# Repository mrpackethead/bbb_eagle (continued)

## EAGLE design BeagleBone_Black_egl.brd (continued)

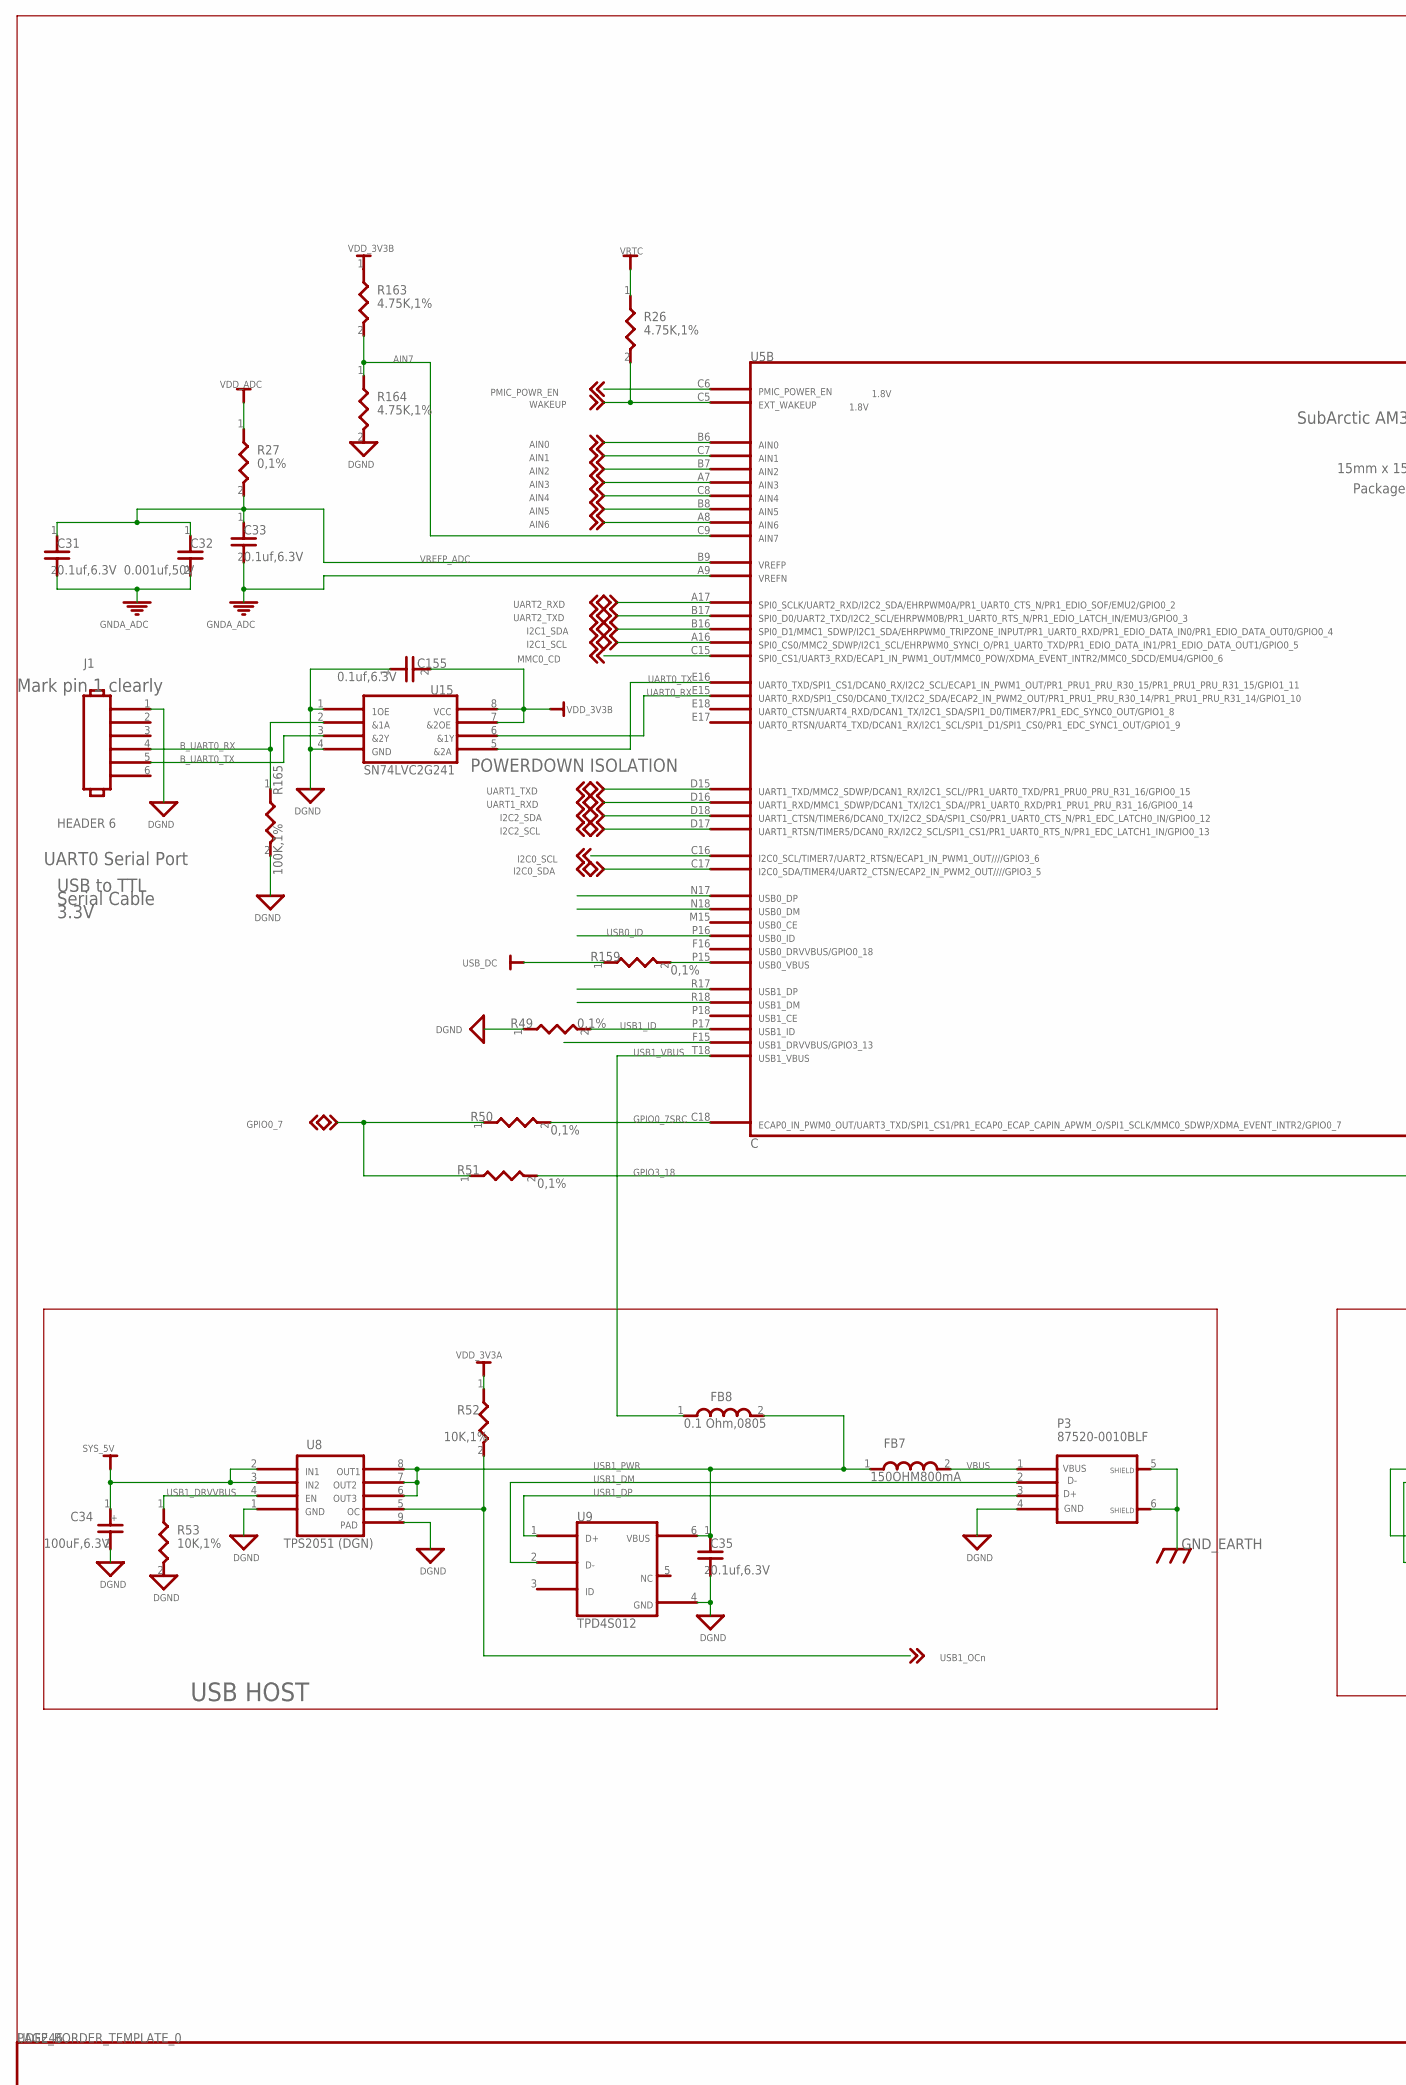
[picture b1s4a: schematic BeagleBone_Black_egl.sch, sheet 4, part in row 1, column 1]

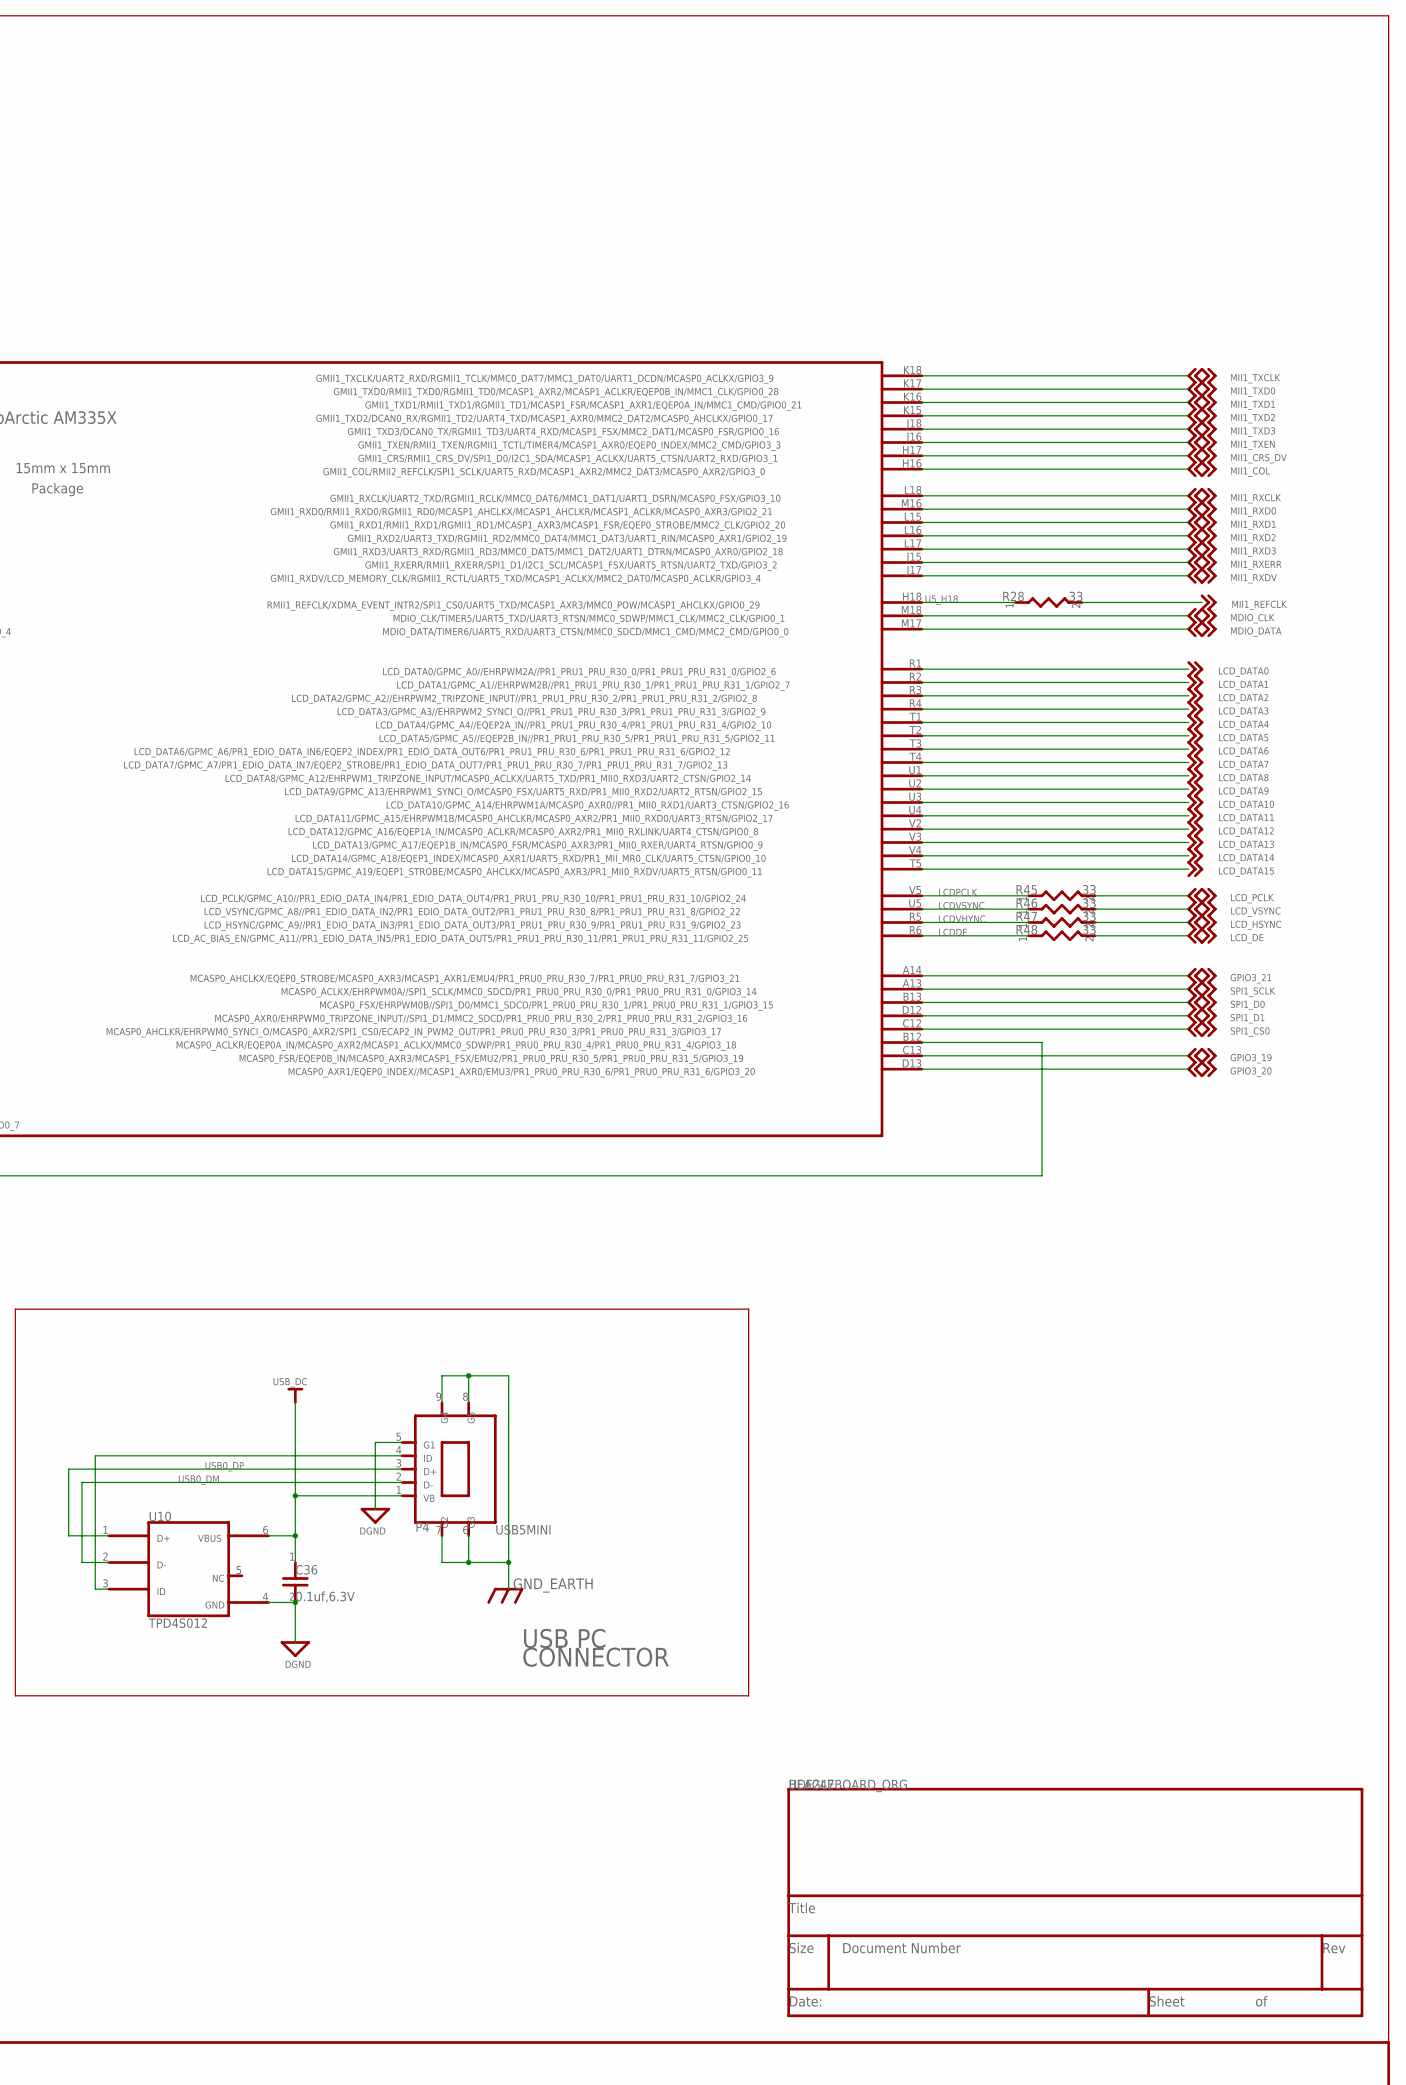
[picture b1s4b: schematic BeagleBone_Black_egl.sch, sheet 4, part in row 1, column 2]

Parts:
C31, C33, C35, C36, C155: 0.1uf,6.3V; 402
C32: 0.001uf,50V; 402
C34: 100uF,6.3V; RD205SMD_250D
FB7: 150OHM800mA; SM-7351-IND-0805
FB8: 0.1 Ohm,0805; SM-7351-IND-0805
J1: HEADER 6; SIP6
P3: 87520-0010BLF; USB_A_SH
P4: USB5MINI; USB5MINI_4SHIELDED_SMD-5
R26, R163, R164: 4.75K,1%; 402
R27, R49, R50, R51, R159: 0,1%; 402
R28, R45, R46, R47, R48: 33; 0402
R52, R53: 10K,1%; 402
R165: 100K,1%; 402
U5: C; AM33XX_15X15
U8: TPS2051 (DGN); DGN-16X60
U9, U10: TPD4S012; U_6_DRY
U15: SN74LVC2G241; U_8_DCU

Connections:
AIN0: U5.B6 (1); also elsewhere on the board
AIN1: U5.C7 (2); also elsewhere on the board
AIN2: U5.B7 (3); also elsewhere on the board
AIN3: U5.A7 (4); also elsewhere on the board
AIN4: U5.C8 (5); also elsewhere on the board
AIN5: U5.B8 (6); also elsewhere on the board
AIN6: U5.A8 (7); also elsewhere on the board
AIN7: R163.2, R164.1, U5.C9 (8)
B_UART0_RX: J1.4, R165.1, U15.2 (1)
B_UART0_TX: J1.5, U15.3 (7)
DGND: C34.2, C35.2, C36.2, C155.1, J1.1, P3.4, P4.5 (7), R49.1, R53.2, R164.2, R165.2, U8.1, U8.9, U9.4, U10.4, U15.1 (3), U15.4 (5); also elsewhere on the board
GNDA_ADC: C31.2, C32.2, C33.2, U5.A9 (10); also elsewhere on the board
GND_EARTH: P3.5, P3.6, P4.6, P4.7 (5), P4.8, P4.9; also elsewhere on the board
GPIO0_7: R50.1, R51.1; also elsewhere on the board
GPIO0_7SRC: R50.2, U5.C18 (86)
GPIO3_18: R51.2, U5.B12 (83)
GPIO3_19: U5.C13 (84); also elsewhere on the board
GPIO3_20: U5.D13 (85); also elsewhere on the board
GPIO3_21: U5.A14 (78); also elsewhere on the board
I2C0_SCL: U5.C16 (49); also elsewhere on the board
I2C0_SDA: U5.C17 (50); also elsewhere on the board
I2C1_SCL: U5.A16 (74); also elsewhere on the board
I2C1_SDA: U5.B16 (73); also elsewhere on the board
I2C2_SCL: U5.D17 (48); also elsewhere on the board
I2C2_SDA: U5.D18 (47); also elsewhere on the board
LCDDE: R48.1, U5.R6 (70)
LCDPCLK: R45.1, U5.V5 (67)
LCDVHYNC: R47.1, U5.R5 (69)
LCDVSYNC: R46.1, U5.U5 (68)
LCD_DATA0: U5.R1 (51); also elsewhere on the board
LCD_DATA1: U5.R2 (52); also elsewhere on the board
LCD_DATA2: U5.R3 (53); also elsewhere on the board
LCD_DATA3: U5.R4 (54); also elsewhere on the board
LCD_DATA4: U5.T1 (55); also elsewhere on the board
LCD_DATA5: U5.T2 (56); also elsewhere on the board
LCD_DATA6: U5.T3 (57); also elsewhere on the board
LCD_DATA7: U5.T4 (58); also elsewhere on the board
LCD_DATA8: U5.U1 (59); also elsewhere on the board
LCD_DATA9: U5.U2 (60); also elsewhere on the board
LCD_DATA10: U5.U3 (61); also elsewhere on the board
LCD_DATA11: U5.U4 (62); also elsewhere on the board
LCD_DATA12: U5.V2 (63); also elsewhere on the board
LCD_DATA13: U5.V3 (64); also elsewhere on the board
LCD_DATA14: U5.V4 (65); also elsewhere on the board
LCD_DATA15: U5.T5 (66); also elsewhere on the board
LCD_DE: R48.2; also elsewhere on the board
LCD_HSYNC: R47.2; also elsewhere on the board
LCD_PCLK: R45.2; also elsewhere on the board
LCD_VSYNC: R46.2; also elsewhere on the board
MDIO_CLK: U5.M18 (43); also elsewhere on the board
MDIO_DATA: U5.M17 (44); also elsewhere on the board
MII1_COL: U5.H16 (27); also elsewhere on the board
MII1_CRS_DV: U5.H17 (28); also elsewhere on the board
MII1_REFCLK: R28.2; also elsewhere on the board
MII1_RXCLK: U5.L18 (37); also elsewhere on the board
MII1_RXD0: U5.M16 (38); also elsewhere on the board
MII1_RXD1: U5.L15 (39); also elsewhere on the board
MII1_RXD2: U5.L16 (40); also elsewhere on the board
MII1_RXD3: U5.L17 (41); also elsewhere on the board
MII1_RXDV: U5.J17 (36); also elsewhere on the board
MII1_RXERR: U5.J15 (35); also elsewhere on the board
MII1_TXCLK: U5.K18 (33); also elsewhere on the board
MII1_TXD0: U5.K17 (29); also elsewhere on the board
MII1_TXD1: U5.K16 (30); also elsewhere on the board
MII1_TXD2: U5.K15 (31); also elsewhere on the board
MII1_TXD3: U5.J18 (32); also elsewhere on the board
MII1_TXEN: U5.J16 (34); also elsewhere on the board
MMC0_CD: U5.C15 (75); also elsewhere on the board
N22155575: R159.2, U5.P15 (18)
PMIC_POWR_EN: U5.C6 (76); also elsewhere on the board
SPI1_CS0: U5.C12 (82); also elsewhere on the board
SPI1_D0: U5.B13 (80); also elsewhere on the board
SPI1_D1: U5.D12 (81); also elsewhere on the board
SPI1_SCLK: U5.A13 (79); also elsewhere on the board
SYS_5V: C34.1, U8.2, U8.3; also elsewhere on the board
U5_H18: R28.1, U5.H18 (42)
UART0_RX: U5.E15 (12), U15.6 (8)
UART0_TX: U5.E16 (11), U15.5 (6)
UART1_RXD: U5.D16 (46); also elsewhere on the board
UART1_TXD: U5.D15 (45); also elsewhere on the board
UART2_RXD: U5.A17 (71); also elsewhere on the board
UART2_TXD: U5.B17 (72); also elsewhere on the board
USB0_DM: P4.2 (1), U5.N18 (16), U10.2
USB0_DP: P4.3 (2), U5.N17 (15), U10.1
USB0_ID: P4.4, U5.P16 (23), U10.3 (6)
USB1_DM: P3.2 (3), U5.R18 (21), U9.2
USB1_DP: P3.3 (2), U5.R17 (20), U9.1
USB1_DRVVBUS: R53.1, U5.F15 (26), U8.4
USB1_ID: R49.2, U5.P17 (22)
USB1_OCN: R52.2, U8.5 (8); also elsewhere on the board
USB1_PWR: C35.1, FB7.1, FB8.2, U8.6 (5), U8.7 (6), U8.8 (7), U9.6 (3)
USB1_VBUS: FB8.1, U5.T18 (25)
USB_DC: C36.1, P4.1 (3), R159.1, U10.6 (3); also elsewhere on the board
VBUS: FB7.2, P3.1
VDD_3V3A: R52.1; also elsewhere on the board
VDD_3V3B: C155.2, R163.1, U15.7 (2), U15.8 (4); also elsewhere on the board
VDD_ADC: R27.1; also elsewhere on the board
VREFP_ADC: C31.1, C32.1, C33.1, R27.2, U5.B9 (9)
VRTC: R26.1; also elsewhere on the board
WAKEUP: R26.2, U5.C5 (77); also elsewhere on the board

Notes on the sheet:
USB HOST
USB PC
CONNECTOR
UART0 Serial Port
USB to TTL
Serial Cable
3.3V
Mark pin 1 clearly
POWERDOWN ISOLATION
DGND
GND_EARTH
I2C0_SCL
I2C0_SDA
PMIC_POWR_EN
SYS_5V
USB_DC
VDD_3V3A
VDD_3V3B
VRTC
WAKEUP
GPIO3_20
GPIO3_21
MMC0_CD
USB1_OCn
AIN0
AIN1
AIN2
AIN3
AIN4
AIN5
AIN6
AIN7
B_UART0_RX
B_UART0_TX
GNDA_ADC
GPIO0_7
GPIO0_7SRC
GPIO3_18
GPIO3_19
I2C1_SCL

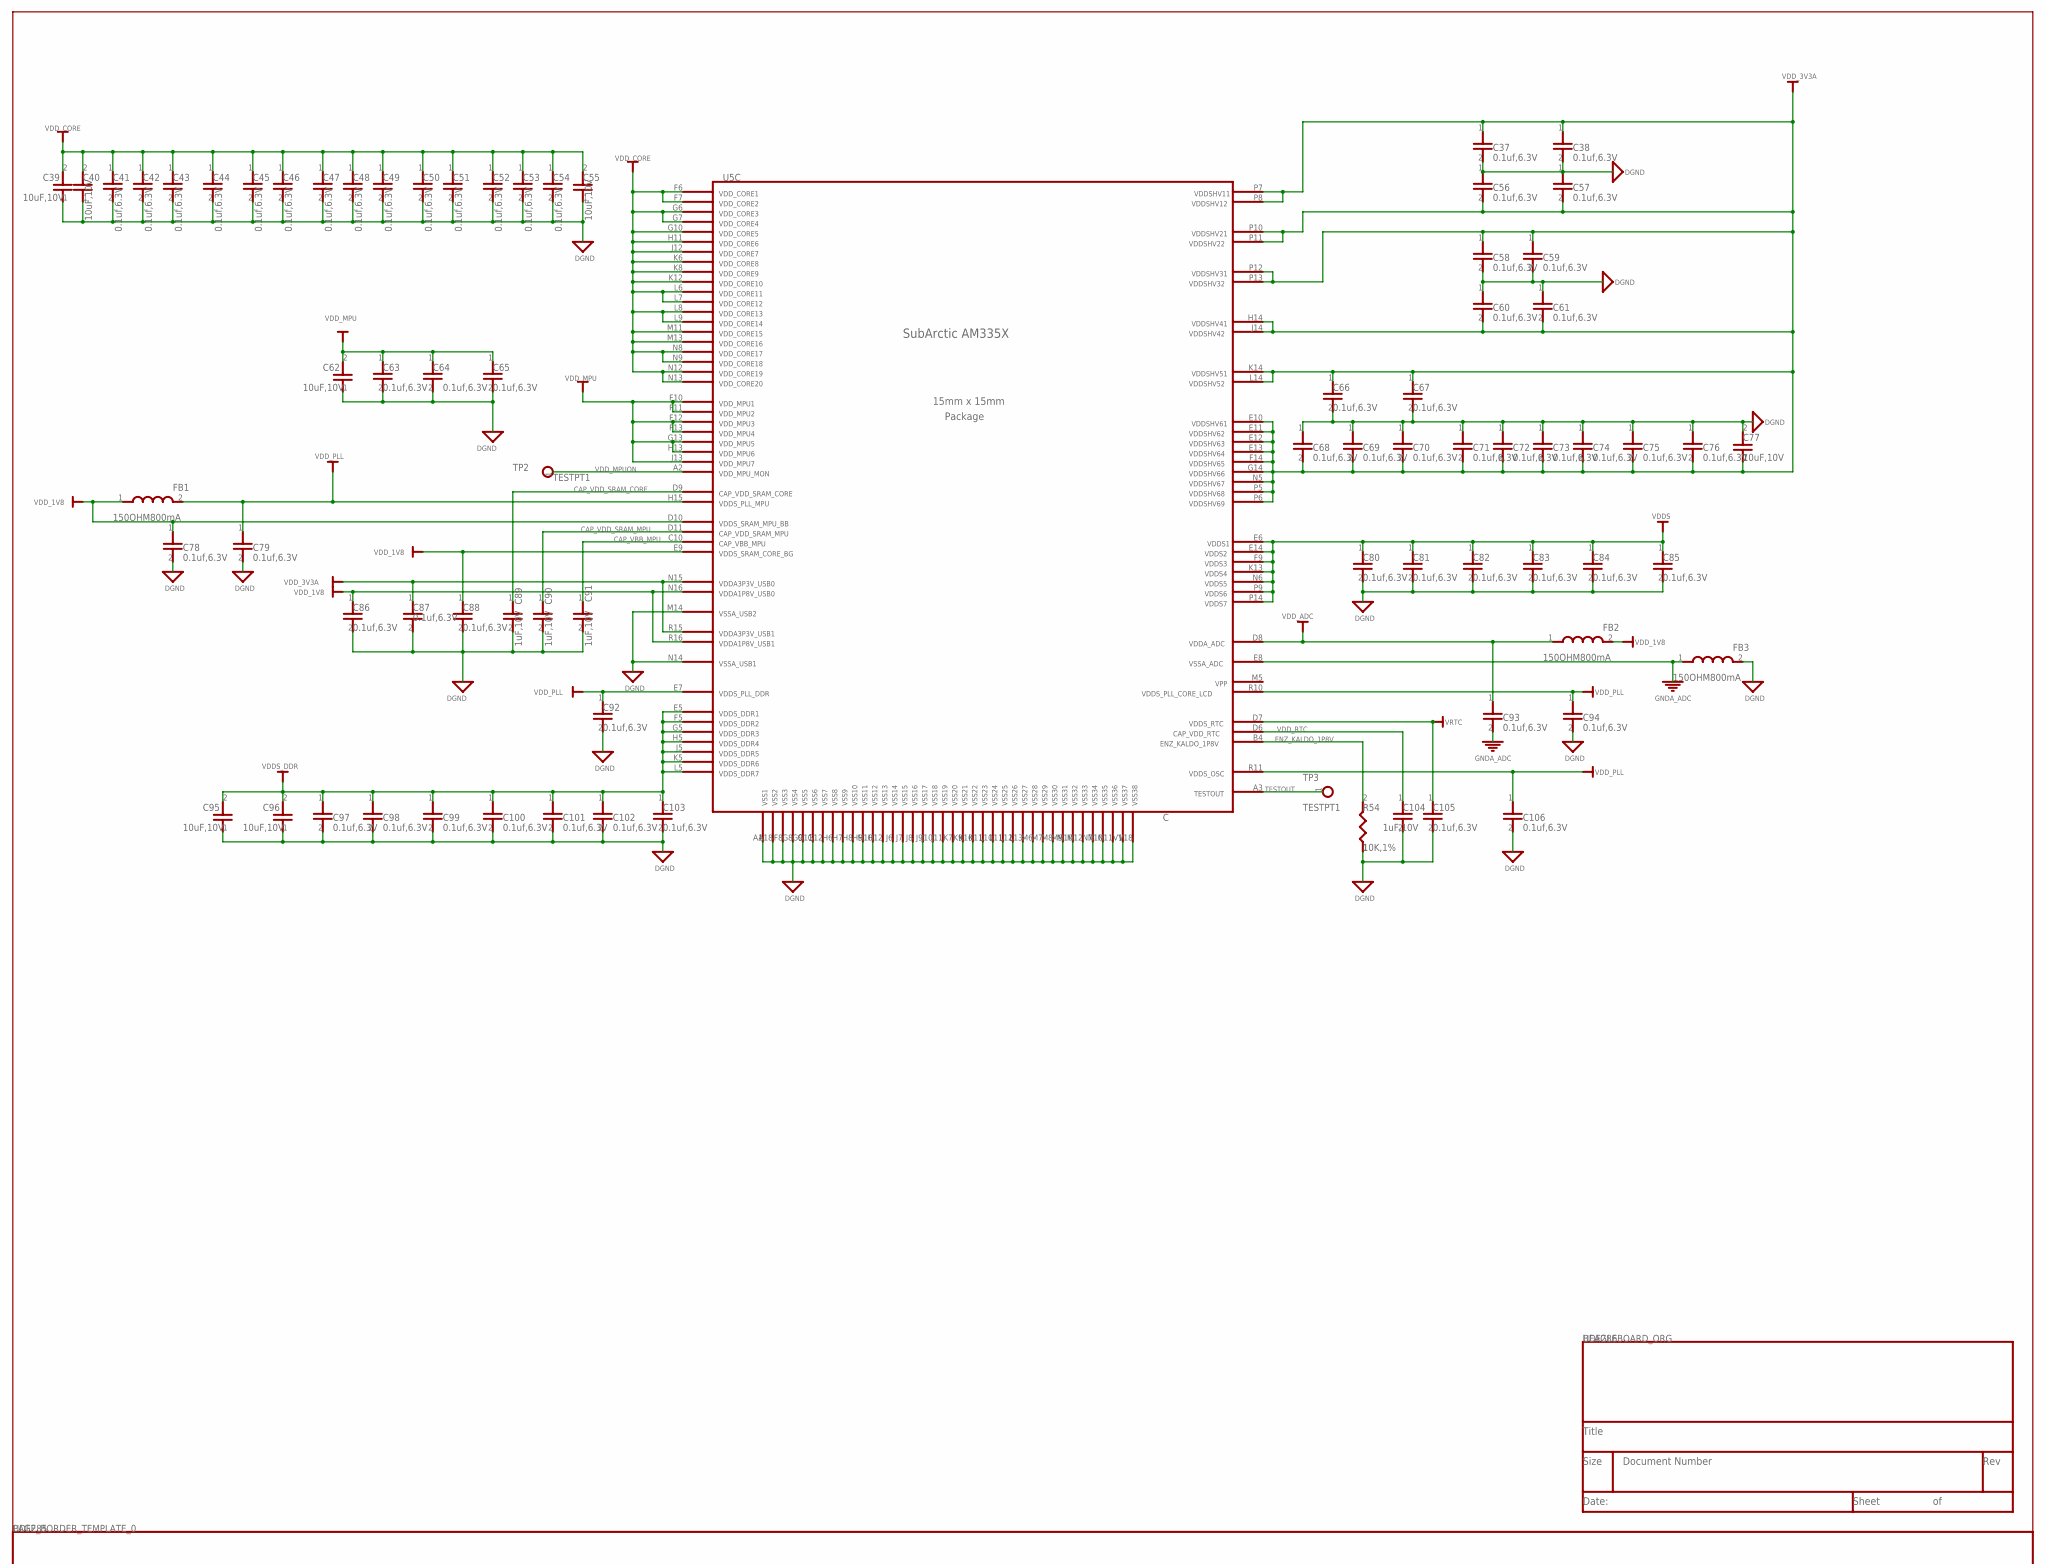
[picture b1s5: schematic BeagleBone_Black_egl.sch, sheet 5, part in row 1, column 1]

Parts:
C37, C38, C41, C42, C43, C44, C45, C46, C47, C48, C49, C50, C51, C52, C53, C54, C56, C57, C58, C59, C60, C61, C63, C64, C65, C66, C67, C68, C69, C70, C71, C72, C73, C74, C75, C76, C78, C79, C80, C81, C82, C83, C84, C85, C86, C87, C88, C92, C93, C94, C97, C98, C99, C100, C101, C102, C103, C105, C106: 0.1uf,6.3V; 402
C39, C40, C55, C62, C77, C95, C96: 10uF,10V; 805
C89, C90, C91, C104: 1uF,10V; 402
FB1, FB2, FB3: 150OHM800mA; SM-7351-IND-0805
R54: 10K,1%; 402
TP2, TP3: TESTPT1; TP60C_SMD
U5: C; AM33XX_15X15

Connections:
CAP_VBB_MPU: C91.1, U5.C10 (76)
CAP_VDD_SRAM_CORE: C89.1, U5.D9 (68)
CAP_VDD_SRAM_MPU: C90.1, U5.D11 (77)
DGND: C37.2, C38.2, C39.1, C40.1, C41.2, C42.2, C43.2, C44.2, C45.2, C46.2, C47.2, C48.2, C49.2, C50.2, C51.2, C52.2, C53.2, C54.2, C55.1, C56.1, C57.1, C58.2, C59.2, C60.1, C61.1, C62.1, C63.2, C64.2, C65.2, C66.2, C67.2, C68.1, C69.1, C70.1, C71.1, C72.1, C73.1, C74.1, C75.1, C76.1, C77.2, C78.2, C79.2, C80.2, C81.2, C82.2, C83.2, C84.2, C85.2, C86.2, C87.2, C88.2, C89.2, C90.2, C91.2, C92.2, C94.2, C95.1, C96.1, C97.2, C98.2, C99.2, C100.2, C101.2, C102.2, C103.2, C104.2, C105.2, C106.2, FB3.2, R54.1, U5.A1 (1), U5.A18 (2), U5.F8 (4), U5.G8 (6), U5.G9 (5), U5.G11 (14), U5.G12 (101), U5.H6 (7), U5.H7 (16), U5.H8 (18), U5.H9 (8), U5.H10 (9), U5.H12 (15), U5.J6 (24), U5.J7 (10), U5.J8 (11), U5.J9 (12), U5.J10 (13), U5.J11 (27), U5.K7 (17), U5.K9 (19), U5.K10 (20), U5.K11 (21), U5.L10 (35), U5.L11 (23), U5.L12 (29), U5.L13 (36), U5.M6 (25), U5.M7 (26), U5.M8 (3), U5.M9 (28), U5.M10 (30), U5.M12 (22), U5.M14 (85), U5.N7 (31), U5.N10 (33), U5.N11 (34), U5.N14 (82), U5.V1 (37), U5.V18 (32); also elsewhere on the board
ENZ_KALDO_1P8V: R54.2, U5.B4 (99)
GNDA_ADC: C93.2, FB3.1, U5.E8 (87); also elsewhere on the board
TESTOUT: TP3.1, U5.A3 (100)
VDDS: C80.1, C81.1, C82.1, C83.1, C84.1, C85.1, U5.E6 (62), U5.E14 (63), U5.F9 (64), U5.K13 (65), U5.N6 (66), U5.P9 (67), U5.P14 (120); also elsewhere on the board
VDDS_DDR: C95.2, C96.2, C97.1, C98.1, C99.1, C100.1, C101.1, C102.1, C103.1, U5.E5 (90), U5.F5 (91), U5.G5 (92), U5.H5 (93), U5.J5 (89), U5.K5 (94), U5.L5 (95); also elsewhere on the board
VDD_1V8: C78.1, C86.1, C88.1, FB1.1, FB2.2, U5.D10 (75), U5.E9 (69), U5.N16 (84), U5.R16 (81); also elsewhere on the board
VDD_3V3A: C37.1, C38.1, C56.2, C57.2, C58.1, C59.1, C60.2, C61.2, C66.1, C67.1, C68.2, C69.2, C70.2, C71.2, C72.2, C73.2, C74.2, C75.2, C76.2, C77.1, C87.1, U5.E10 (111), U5.E11 (112), U5.E12 (113), U5.E13 (114), U5.F14 (115), U5.G14 (116), U5.H14 (59), U5.J14 (58), U5.K14 (60), U5.L14 (61), U5.N5 (117), U5.N15 (83), U5.P5 (118), U5.P6 (119), U5.P7 (53), U5.P8 (54), U5.P10 (55), U5.P11 (96), U5.P12 (56), U5.P13 (57), U5.R15 (80); also elsewhere on the board
VDD_ADC: C93.1, FB2.1, U5.D8 (72); also elsewhere on the board
VDD_CORE: C39.2, C40.2, C41.1, C42.1, C43.1, C44.1, C45.1, C46.1, C47.1, C48.1, C49.1, C50.1, C51.1, C52.1, C53.1, C54.1, C55.2, U5.F6 (38), U5.F7 (39), U5.G6 (40), U5.G7 (42), U5.G10 (43), U5.H11 (45), U5.J12 (46), U5.K6 (47), U5.K8 (97), U5.K12 (49), U5.L6 (50), U5.L7 (51), U5.L8 (52), U5.L9 (98), U5.M11 (102), U5.M13 (103), U5.N8 (104), U5.N9 (105), U5.N12 (106), U5.N13 (107); also elsewhere on the board
VDD_MPU: C62.2, C63.1, C64.1, C65.1, U5.F10 (41), U5.F11 (44), U5.F12 (48), U5.F13 (88), U5.G13 (108), U5.H13 (109), U5.J13 (110); also elsewhere on the board
VDD_MPUON: TP2.1, U5.A2 (121)
VDD_PLL: C79.1, C92.1, C94.1, C106.1, FB1.2, U5.E7 (86), U5.H15 (79), U5.R10 (71), U5.R11 (70)
VDD_RTC: C104.1, U5.D6 (73)
VRTC: C105.1, U5.D7 (74); also elsewhere on the board

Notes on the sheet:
DGND
VDDS
VDDS_DDR
VDD_1V8
VDD_3V3A
VDD_CORE
VDD_MPU
VRTC
GNDA_ADC
VDD_ADC
CAP_VBB_MPU
CAP_VDD_SRAM_CORE
CAP_VDD_SRAM_MPU
ENZ_KALDO_1P8V
TESTOUT
VDD_MPUON
VDD_PLL
VDD_RTC

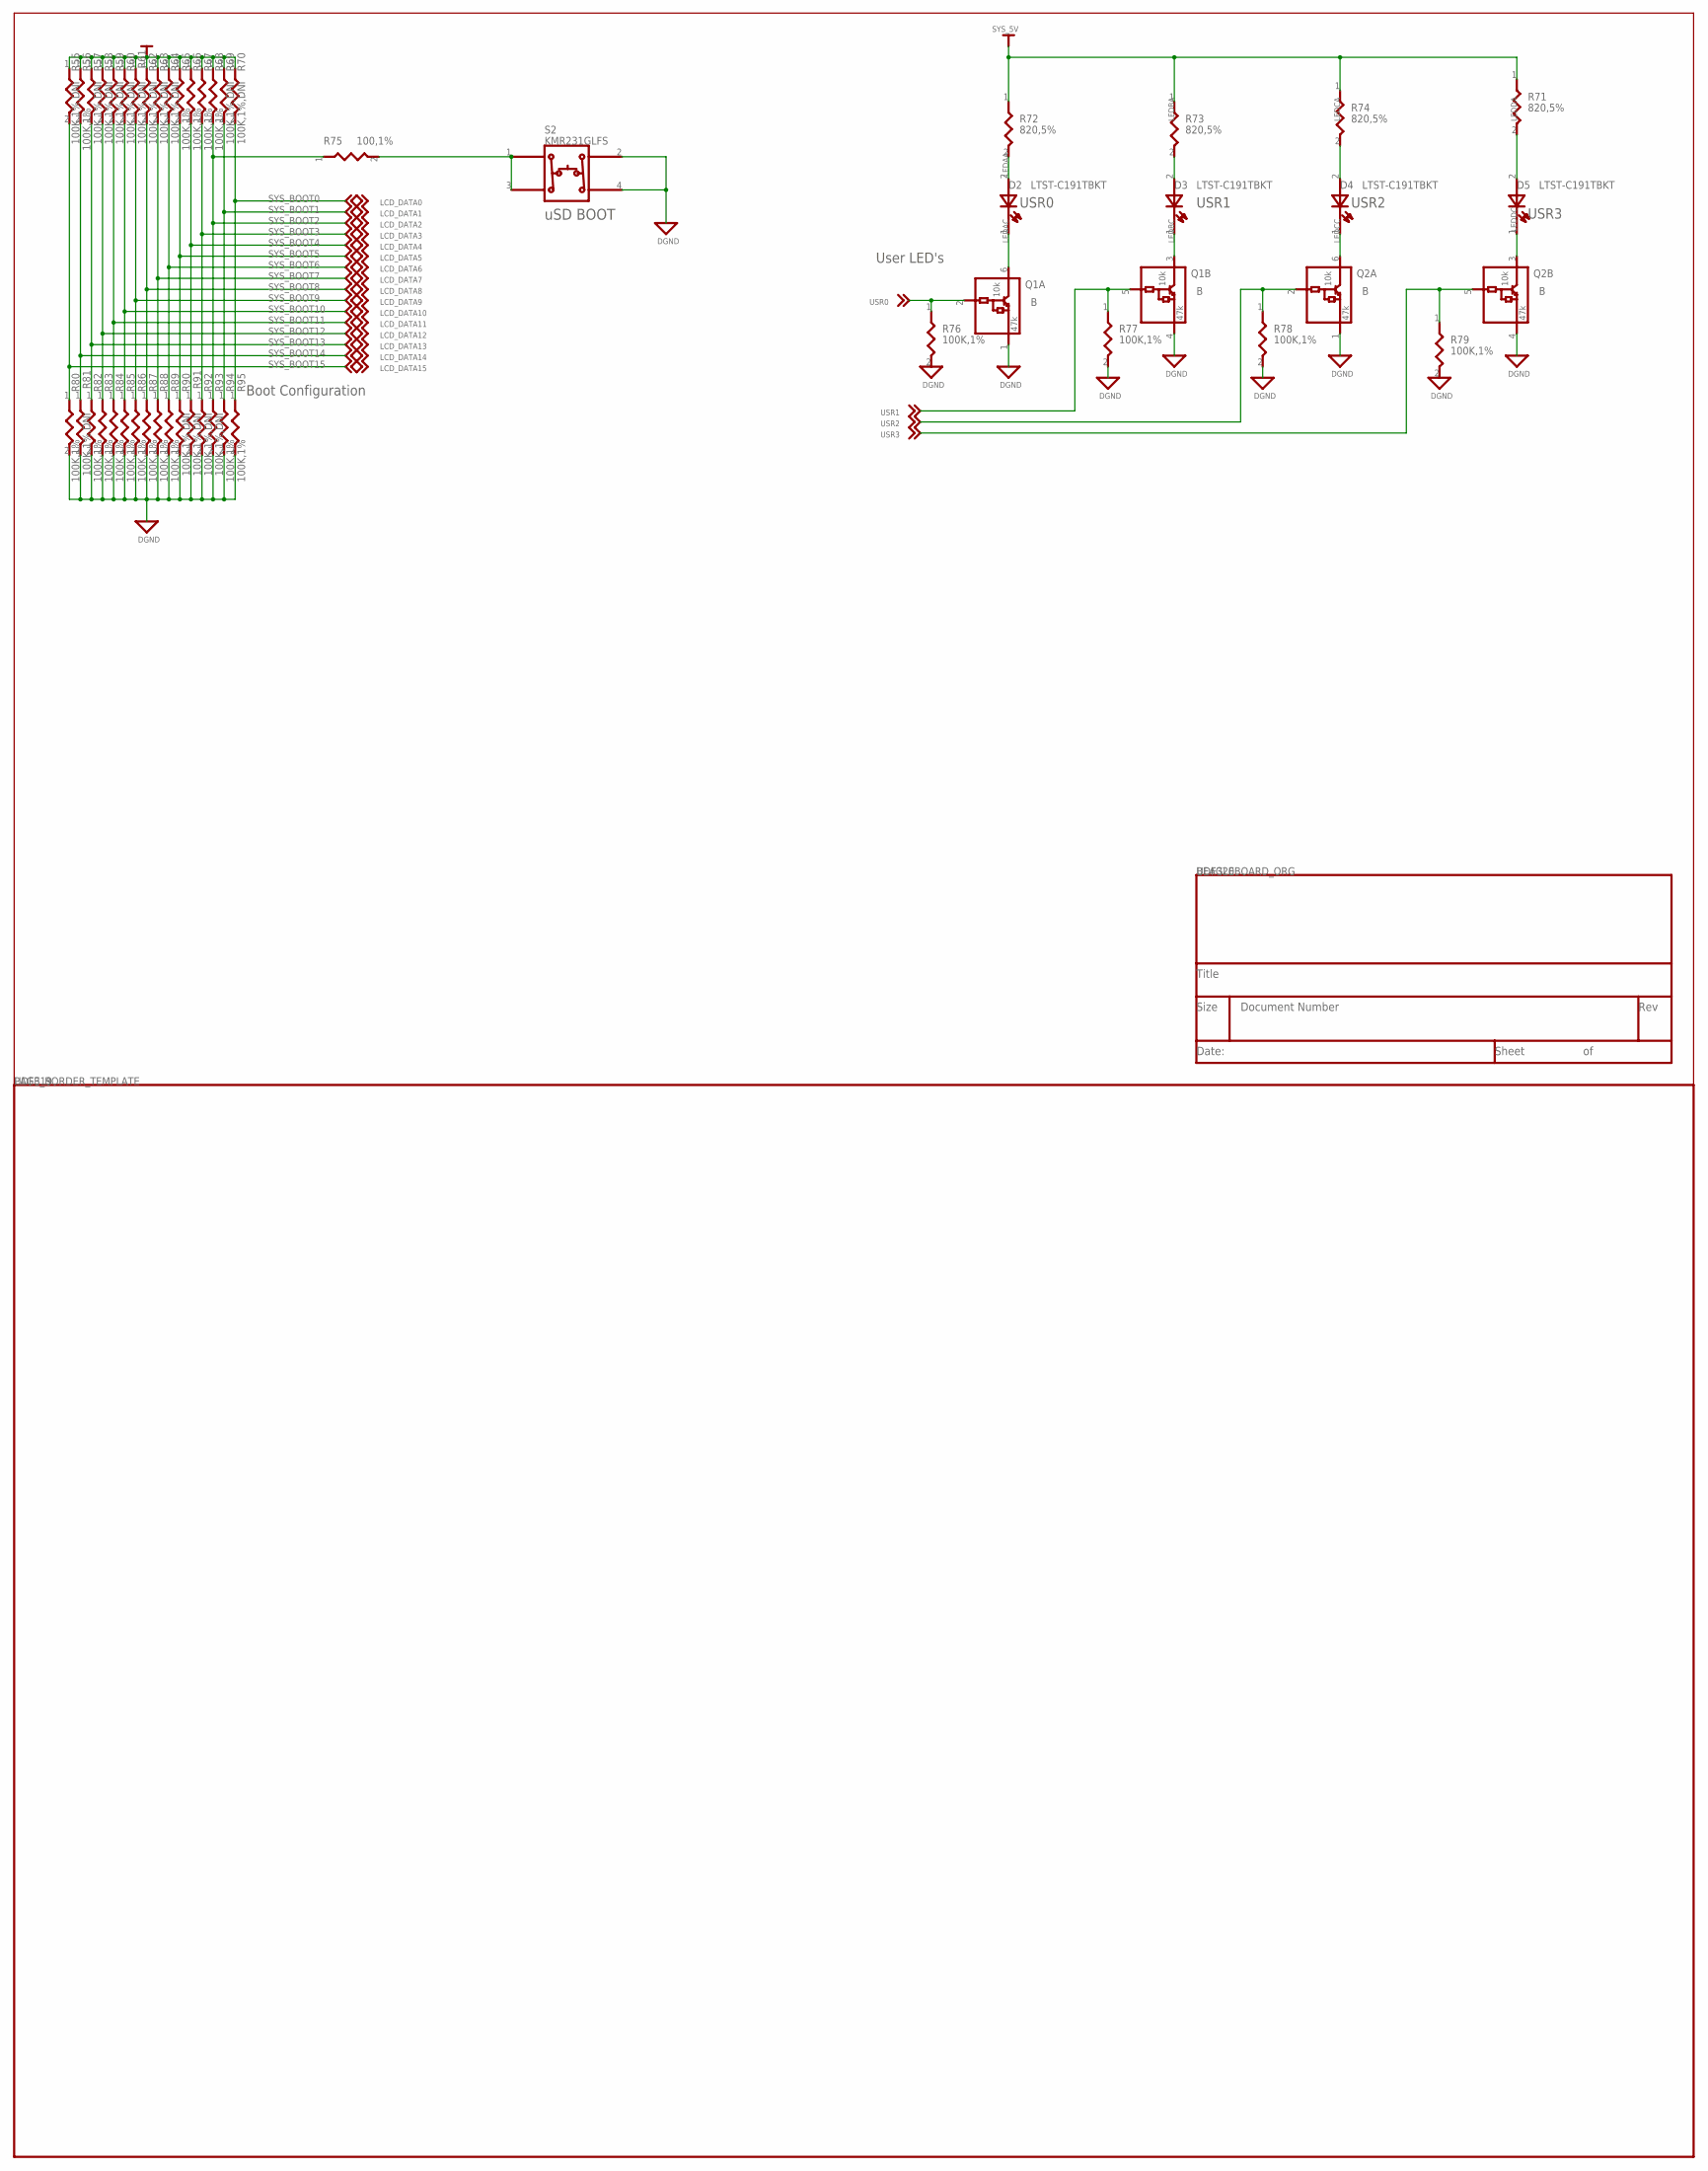
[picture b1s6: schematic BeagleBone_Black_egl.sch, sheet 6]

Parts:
D2, D3, D4, D5: LTST-C191TBKT; LED_0603
Q1, Q2: B; SMINI6-F3-B
R55, R57, R58, R59, R60, R61, R62, R63, R64, R69, R70, R81, R90, R91, R92, R93: 100K,1%,DNI; 402
R56, R65, R66, R67, R68, R76, R77, R78, R79, R80, R82, R83, R84, R85, R86, R87, R88, R89, R94, R95: 100K,1%; 402
R71, R72, R73, R74: 820,5%; 402
R75: 100,1%; 402
S2: KMR231GLFS; SW4SMD_63X161LS

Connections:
DGND: Q1.1, Q1.4 (1), Q2.1, Q2.4 (1), R76.2, R77.2, R78.2, R79.2, R80.2, R81.2, R82.2, R83.2, R84.2, R85.2, R86.2, R87.2, R88.2, R89.2, R90.2, R91.2, R92.2, R93.2, R94.2, R95.2, S2.2, S2.4; also elsewhere on the board
LCD_DATA0: R70.2, R95.1; also elsewhere on the board
LCD_DATA1: R69.2, R94.1; also elsewhere on the board
LCD_DATA2: R68.2, R75.1, R93.1; also elsewhere on the board
LCD_DATA3: R67.2, R92.1; also elsewhere on the board
LCD_DATA4: R66.2, R91.1; also elsewhere on the board
LCD_DATA5: R65.2, R90.1; also elsewhere on the board
LCD_DATA6: R64.2, R89.1; also elsewhere on the board
LCD_DATA7: R63.2, R88.1; also elsewhere on the board
LCD_DATA8: R62.2, R87.1; also elsewhere on the board
LCD_DATA9: R61.2, R86.1; also elsewhere on the board
LCD_DATA10: R60.2, R85.1; also elsewhere on the board
LCD_DATA11: R59.2, R84.1; also elsewhere on the board
LCD_DATA12: R58.2, R83.1; also elsewhere on the board
LCD_DATA13: R57.2, R82.1; also elsewhere on the board
LCD_DATA14: R56.2, R81.1; also elsewhere on the board
LCD_DATA15: R55.2, R80.1; also elsewhere on the board
LEDAA: D2.2, R72.2
LEDAC: D2.1, Q1.6 (2)
LEDBA: D3.2, R73.2
LEDBC: D3.1, Q1.3 (2)
LEDCA: D4.2, R74.2
LEDCC: D4.1, Q2.6 (2)
LEDDA: D5.2, R71.2
LEDDC: D5.1, Q2.3 (2)
N21769115: R75.2, S2.1, S2.3
SYS_5V: R71.1, R72.1, R73.1, R74.1; also elsewhere on the board
USR0: Q1.2 (3), R76.1; also elsewhere on the board
USR1: Q1.5 (3), R77.1; also elsewhere on the board
USR2: Q2.2 (3), R78.1; also elsewhere on the board
USR3: Q2.5 (3), R79.1; also elsewhere on the board
VDD_3V3A: R55.1, R56.1, R57.1, R58.1, R59.1, R60.1, R61.1, R62.1, R63.1, R64.1, R65.1, R66.1, R67.1, R68.1, R69.1, R70.1; also elsewhere on the board

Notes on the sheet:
SYS_BOOT8
SYS_BOOT9
SYS_BOOT10
SYS_BOOT11
SYS_BOOT12
SYS_BOOT13
SYS_BOOT14
SYS_BOOT15
SYS_BOOT4
User LED's
Boot Configuration
SYS_BOOT0
SYS_BOOT1
SYS_BOOT2
SYS_BOOT3
SYS_BOOT5
SYS_BOOT6
SYS_BOOT7
USR0
USR1
USR2
USR3
uSD BOOT
DGND
SYS_5V
USR0
USR1
USR2
USR3
LCD_DATA0
LCD_DATA1
LCD_DATA10
LCD_DATA11
LCD_DATA12
LCD_DATA13
LCD_DATA14
LCD_DATA15
LCD_DATA2
LCD_DATA3
LCD_DATA4
